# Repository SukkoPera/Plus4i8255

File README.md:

# Plus4i8255
Plus4i8255 is an Intel 8255 Interface for the Commodore 16, 116 and Plus/4.

## Summary
The Intel 8255 is a general purpose programmable I/O device featuring 24 I/O pins which may be individually programmed in 2 groups
of 12 and used in 3 major modes of operation.

Plus4i8255 is based on the [article published in Rádiótechnika 1988/12](https://plus4world.powweb.com/publications/Radiotechnika_1988_december) by Ferenc Garay and Dr. János Rohonczy with a few improvements: the board has been made much smaller, the ICs doing address decoding have been turned into a GAL for easy reconfigurability (both GAL20 and GAL22 are supported) and pull-up resistors have been added on all inputs.

## Assembly
Intel 8255 chips can all be bought supercheap on AliExpress & similar sites. There are only a couple of other components, making this board very affordable to build for everyone.

## Software
The board is generic and can be used for a multitude of purposes, but its most common usage back in the day was to connect a 1541 drive in a parallel fashion, making it faster when used with software such as [Port-Turbo V1](https://plus4world.powweb.com/software/Port-Turbo_V1) or [Port-Backup](https://plus4world.powweb.com/software/Port-Backup).

A simple program to test all the board I/O pins (in Mode 1) can be found in the Release area.

## Programming
The 8255 is a relatively complex chip with 3 different modes of operation. The datasheet is your friend, those for a few different chips are provided in the [doc directory](doc/). Make sure to pick the one corresponding to your target chip and read it carefully.

The board exposes the four 8255 registers at $FE00-$FE03:
|Address | Description
|-----|----------------|
|$FE00|Port A Register |
|$FE01|Port B Register |
|$FE02|Port C Register |
|$FE03|Control Register|

Note that, while on some modern chip all registers can be read and written to, for compatibility's sake you should assume that the Control Register can only be written to, as is the case with most (older) 8255 chips.

## Releases
If you want to get this board produced, you are recommended to get [the latest release](https://github.com/SukkoPera/Plus4i8255/releases) rather than the current git version, as the latter might be under development and is not guaranteed to be working.

Every release is accompanied by its Bill Of Materials (BOM) file and any relevant notes about it, which you are recommended to read carefully.

## License
The Plus4i8255 documentation, including the design itself, is copyright &copy; SukkoPera 2024 and is licensed under the [Creative Commons Attribution-NonCommercial-ShareAlike 4.0 International License](https://creativecommons.org/licenses/by-nc-sa/4.0/).

This documentation is distributed *as is* and WITHOUT ANY EXPRESS OR IMPLIED WARRANTIES whatsoever with respect to its functionality, operability or use, including, without limitation, any implied warranties OF MERCHANTABILITY, SATISFACTORY QUALITY, FITNESS FOR A PARTICULAR PURPOSE or infringement. We expressly disclaim any liability whatsoever for any direct, indirect, consequential, incidental or special damages, including, without limitation, lost revenues, lost profits, losses resulting from business interruption or loss of data, regardless of the form of action or legal theory under which the liability may be asserted, even if advised of the possibility or likelihood of such damages.

## Support the Project
If you want to get some boards manufactured, you can get them from PCBWay through this link:

You get my gratitude and cheap, professionally-made and good quality PCBs, I get some credit that will help with this and [other projects](https://www.pcbway.com/project/member/shareproject/?bmbid=41100). You won't even have to worry about the various PCB options, it's all pre-configured for you!

Also, if you still have to register, [you can use this link](https://www.pcbway.com/setinvite.aspx?inviteid=41100) to get some bonus initial credit (and yield me some more).

You can also buy me a coffee if you want:

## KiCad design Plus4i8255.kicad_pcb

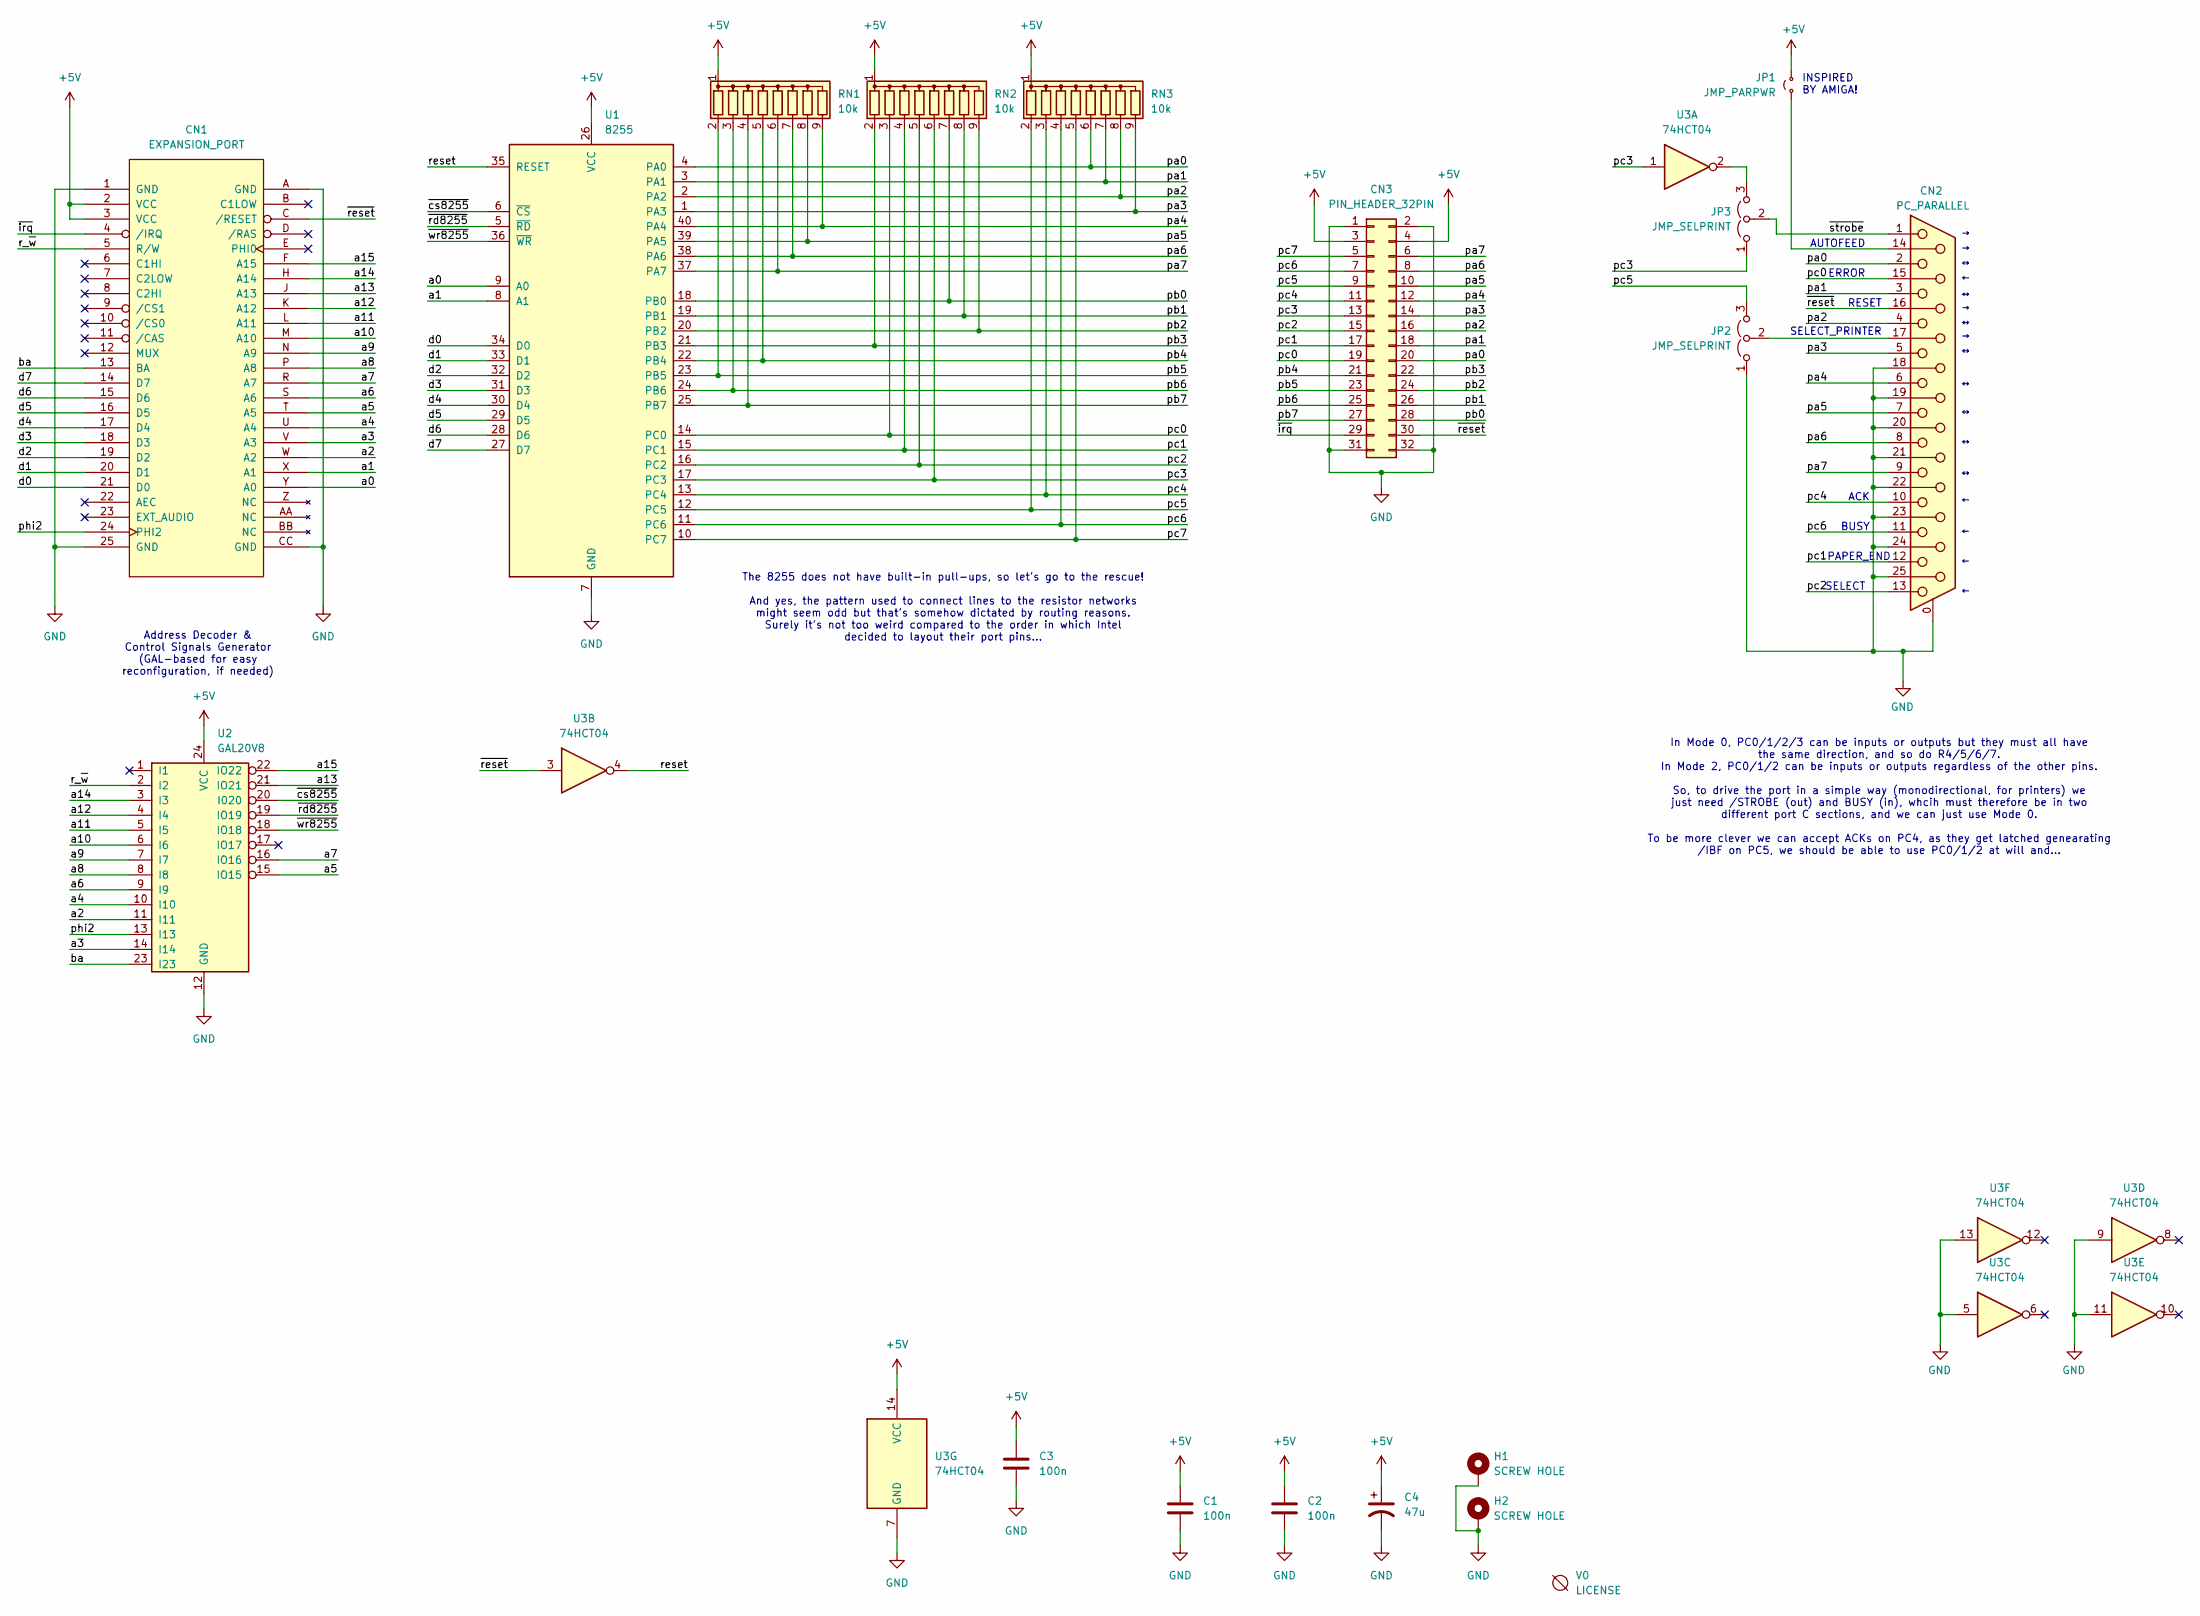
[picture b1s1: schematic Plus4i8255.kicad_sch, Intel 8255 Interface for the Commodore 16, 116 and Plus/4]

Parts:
C1, C2, C3: 100n; C_Disc_D7.0mm_W2.5mm_P5.00mm
C4: 47u; CP_Radial_D5.0mm_P2.00mm
CN1: EXPANSION_PORT; C16_Cart_Conn
CN2: PC_PARALLEL; DSUB-25_Female_Horizontal_P2.77x2.84mm_EdgePinOffset7.70mm_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
CN3: PIN_HEADER_32PIN; PinHeader_2x16_P2.54mm_Vertical
H1, H2: SCREW HOLE; MountingHole_3.2mm_M3_Pad
JP1: JMP_PARPWR; SolderJumper-2_P1.3mm_Open_RoundedPad1.0x1.5mm
JP2, JP3: JMP_SELPRINT; SolderJumper-3_P1.3mm_Open_RoundedPad1.0x1.5mm
RN1, RN2, RN3: 10k; R_Array_SIP9
U1: 8255; DIP-40_W15.24mm_Socket_LongPads
U2: GAL20V8; DIP-24_W7.62mm_Socket_LongPads
U3: 74HCT04; DIP-14_W7.62mm_Socket_LongPads
V0: LICENSE; cc_by_nc_sa

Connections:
+5V: C1.1, C2.1, C3.1, C4.1, CN1.2 (VCC), CN1.3 (VCC), CN3.3, CN3.4, JP1.2 (B), RN1.1 (common), RN2.1 (common), RN3.1 (common), U1.26 (VCC), U2.24 (VCC), U3.14 (VCC)
/a0: CN1.Y (A0), U1.9 (A0)
/a1: CN1.X (A1), U1.8 (A1)
/a2: CN1.W (A2), U2.11 (I11)
/a3: CN1.V (A3), U2.14 (I14)
/a4: CN1.U (A4), U2.10 (I10)
/a5: CN1.T (A5), U2.15 (IO15)
/a6: CN1.S (A6), U2.9 (I9)
/a7: CN1.R (A7), U2.16 (IO16)
/a8: CN1.P (A8), U2.8 (I8)
/a9: CN1.N (A9), U2.7 (I7)
/a10: CN1.M (A10), U2.6 (I6)
/a11: CN1.L (A11), U2.5 (I5)
/a12: CN1.K (A12), U2.4 (I4)
/a13: CN1.J (A13), U2.21 (IO21)
/a14: CN1.H (A14), U2.3 (I3)
/a15: CN1.F (A15), U2.22 (IO22)
/ba: CN1.13 (BA), U2.23 (I23)
/d0: CN1.21 (D0), U1.34 (D0)
/d1: CN1.20 (D1), U1.33 (D1)
/d2: CN1.19 (D2), U1.32 (D2)
/d3: CN1.18 (D3), U1.31 (D3)
/d4: CN1.17 (D4), U1.30 (D4)
/d5: CN1.16 (D5), U1.29 (D5)
/d6: CN1.15 (D6), U1.28 (D6)
/d7: CN1.14 (D7), U1.27 (D7)
/pa0: CN2.2, CN3.20, RN3.6 (R5), U1.4 (PA0)
/pa1: CN2.3, CN3.18, RN3.7 (R6), U1.3 (PA1)
/pa2: CN2.4, CN3.16, RN3.8 (R7), U1.2 (PA2)
/pa3: CN2.5, CN3.14, RN3.9 (R8), U1.1 (PA3)
/pa4: CN2.6, CN3.12, RN1.9 (R8), U1.40 (PA4)
/pa5: CN2.7, CN3.10, RN1.8 (R7), U1.39 (PA5)
/pa6: CN2.8, CN3.8, RN1.7 (R6), U1.38 (PA6)
/pa7: CN2.9, CN3.6, RN1.6 (R5), U1.37 (PA7)
/pb0: CN3.28, RN2.7 (R6), U1.18 (PB0)
/pb1: CN3.26, RN2.8 (R7), U1.19 (PB1)
/pb2: CN3.24, RN2.9 (R8), U1.20 (PB2)
/pb3: CN3.22, RN2.2 (R1), U1.21 (PB3)
/pb4: CN3.21, RN1.5 (R4), U1.22 (PB4)
/pb5: CN3.23, RN1.2 (R1), U1.23 (PB5)
/pb6: CN3.25, RN1.3 (R2), U1.24 (PB6)
/pb7: CN3.27, RN1.4 (R3), U1.25 (PB7)
/pc0: CN2.15, CN3.19, RN2.3 (R2), U1.14 (PC0)
/pc1: CN2.12, CN3.17, RN2.4 (R3), U1.15 (PC1)
/pc2: CN2.13, CN3.15, RN2.5 (R4), U1.16 (PC2)
/pc3: CN3.13, JP3.1 (A), RN2.6 (R5), U1.17 (PC3), U3.1
/pc4: CN2.10, CN3.11, RN3.3 (R2), U1.13 (PC4)
/pc5: CN3.9, JP2.3 (B), RN3.2 (R1), U1.12 (PC5)
/pc6: CN2.11, CN3.7, RN3.4 (R3), U1.11 (PC6)
/pc7: CN3.5, RN3.5 (R4), U1.10 (PC7)
/phi2: CN1.24 (PHI2), U2.13 (I13)
/r_~w: CN1.5 (R/W), U2.2 (I2)
/reset: U1.35 (RESET), U3.4
/~cs8255: U1.6 (~CS), U2.20 (I020)
/~irq: CN1.4 (/IRQ), CN3.29
/~rd8255: U1.5 (~RD), U2.19 (IO19)
/~reset: CN1.C (/RESET), CN2.16, CN3.30, U3.3
/~strobe: CN2.1, JP3.2 (C)
/~wr8255: U1.36 (~WR), U2.18 (IO18)
GND: C1.2, C2.2, C3.2, C4.2, CN1.1 (GND), CN1.25 (GND), CN1.A (GND), CN1.CC (GND), CN2.0 (PAD), CN2.18, CN2.19, CN2.20, CN2.21, CN2.22, CN2.23, CN2.24, CN2.25, CN3.1, CN3.2, CN3.31, CN3.32, H1.1, H2.1, JP2.1 (A), U1.7 (GND), U2.12 (GND), U3.5, U3.7 (GND), U3.9, U3.11, U3.13
unnamed: CN2.14, JP1.1 (A)
unnamed: CN2.17, JP2.2 (C)
unnamed: JP3.3 (B), U3.2

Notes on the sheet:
Address Decoder & Control Signals Generator (GAL-based for easy reconfiguration, if needed)
In Mode 0, PC0/1/2/3 can be inputs or outputs but they must all have the same direction, and so do R4/5/6/7. In Mode 2, PC0/1/2 can be inputs or outputs regardless of the other pins. So, to drive the port in a simple way (monodirectional, for printers) we just need /STROBE (out) and BUSY (in), whci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
ERROR
RESET
BUSY
ACK
SELECT_PRINTER
The 8255 does not have built-in pull-ups, so let's go to the rescue! And yes, the pattern used to connect lines to the resistor networks might seem odd but that's somehow dictated by routing reasons. Surely it's not too weird compared to the order in which Intel decided to layout their port pins...
INSPIRED BY AMIGA!
SELECT
AUTOFEED
PAPER_END

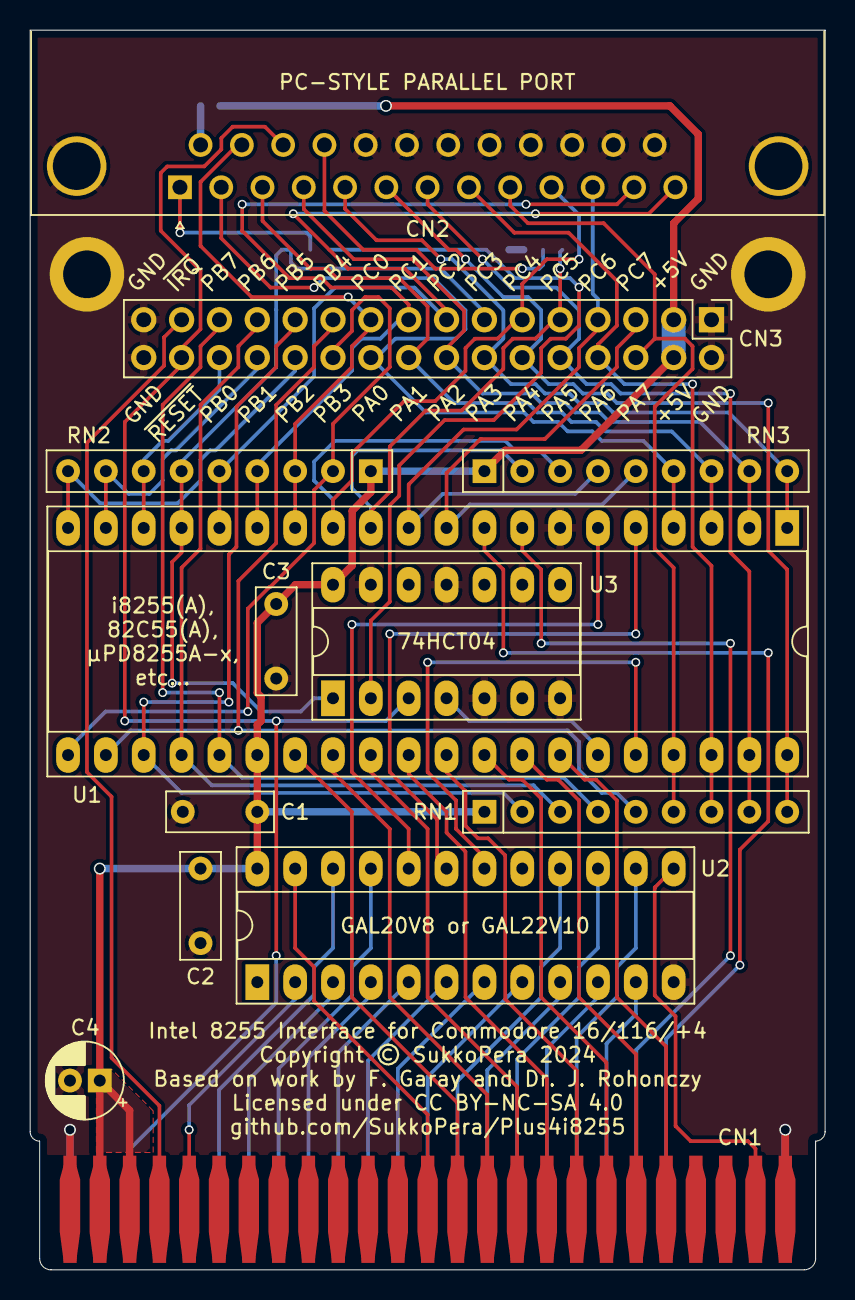
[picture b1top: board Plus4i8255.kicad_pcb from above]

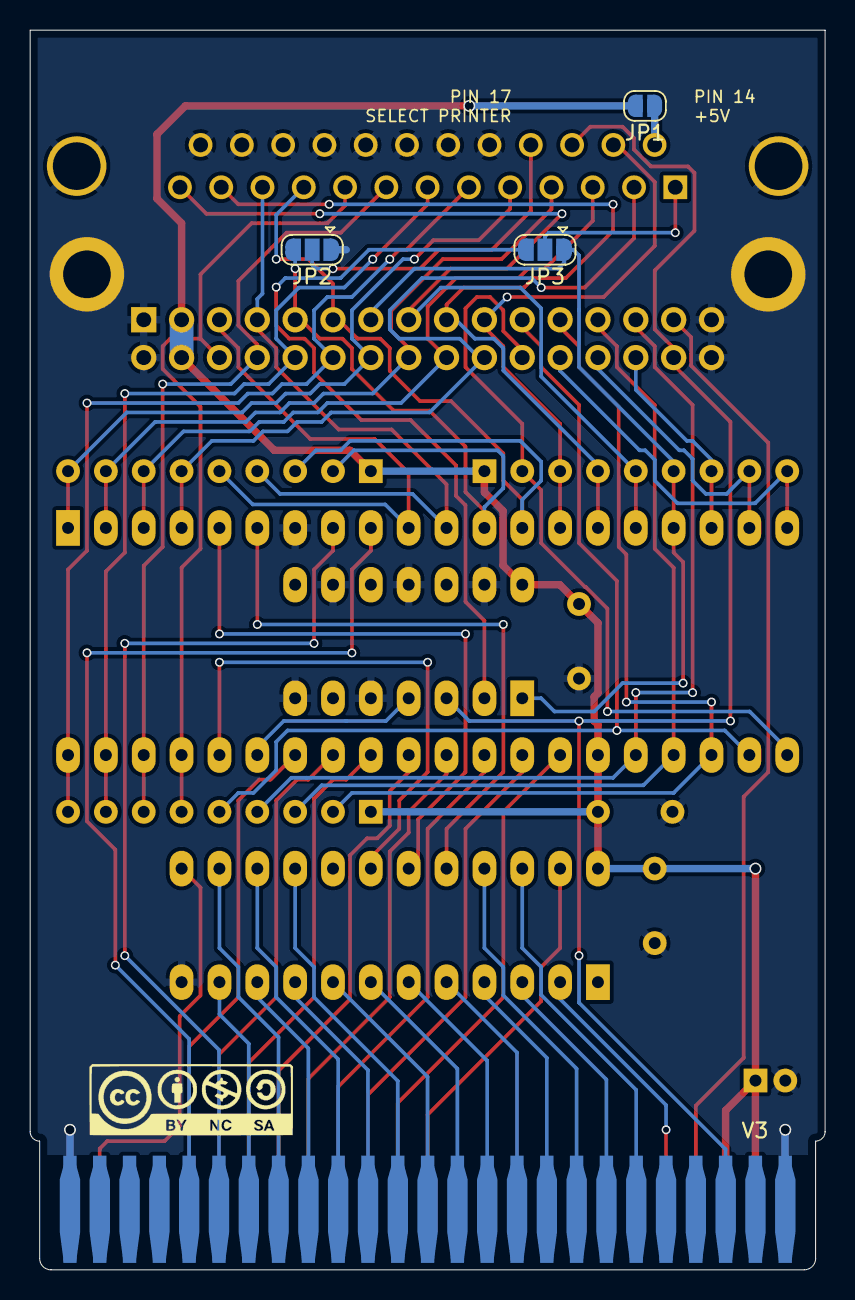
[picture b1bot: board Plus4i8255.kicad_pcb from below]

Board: 2 copper layers, 53.3 x 83.2 mm, 19 parts (4 on the bottom side), 63 nets.

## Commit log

2024-07-13 Almost 1:1 clone of original board
2024-07-13 Add decoupling caps
2024-07-13 Add alternative pin header
2024-07-14 Make less than 10x10cm and add screw holes
2024-07-14 Replace cartridge connector
2024-08-08 Who knows?
2024-08-08 Fix connector symbol and ERC
2024-08-08 Add docs
2024-08-08 Replace all logic with a GAL and make muuuuch smaller
2024-08-08 Final touches
2024-08-08 Add preliminary GAL equations
2024-08-09 (Very) Final touches Note project URL is still missing!
2024-08-19 Add pull-ups on all 8255 ports
2024-08-19 Rework some tracks
2024-08-20 Minor tweaks + Add URL
2024-12-28 Add renders
2024-12-30 Update GAL equations for latest board
2024-12-30 Add GAL22 files (untested)
2024-12-30 TurboFloppy -> Plus4i8255
2024-12-30 Add README
2025-02-14 Add PC-style DB25 parallel port Inspired by zx_spectrum_parallel_interface by @msolajic TBD: Check DB25 footprint!
2025-02-14 Move some tracks around
2025-02-14 Again
2025-04-16 Ready for V3
2025-05-28 Add examples
2025-06-03 Change pins of PC-style parallel port, hopefully adding potential bidirectional capability
2026-02-13 Update coffee donation link and image in README

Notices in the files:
Plus4i8255.kicad_pcb:
Licensed under CC BY-NC-SA 4.0
